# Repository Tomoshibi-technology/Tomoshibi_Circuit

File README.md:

# Tomoshibi_Circuit

ここは燈の基板フォルダです。

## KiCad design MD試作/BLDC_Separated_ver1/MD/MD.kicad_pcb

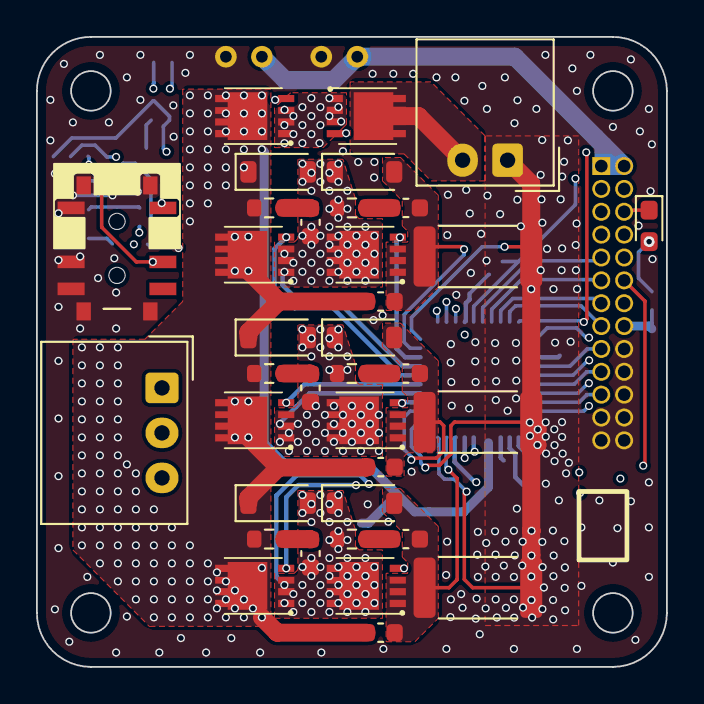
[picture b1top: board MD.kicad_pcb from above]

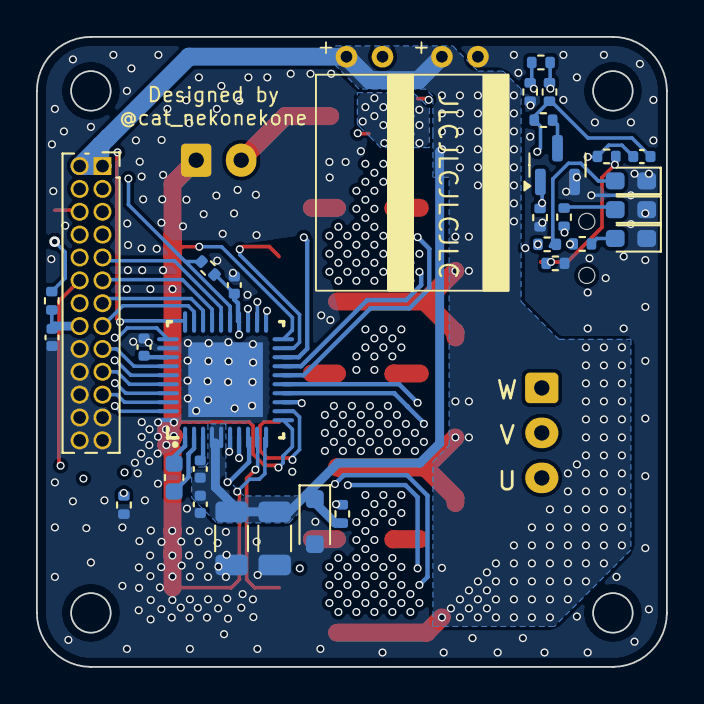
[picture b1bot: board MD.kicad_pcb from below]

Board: 4 copper layers, 35.0 x 35.0 mm, 68 parts (32 on the bottom side), 52 nets.

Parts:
C1, C25, C29: 0.1uF; C_0402_1005Metric
C2, C17: 100uF; Capacitor_Alum_Radial_5.0x11.0mm_Horizontal
C14, C26, C27: 1uF; C_0402_1005Metric
C23, C24: 10uF; C_1206_3216Metric
C28: 47nF; C_0603_1608Metric
C33, C34, C37, C38, C40, C41: CR_snub; C_0603_1608Metric
C35, C36, C39: C_snub; C_0603_1608Metric
D1, D20, D21, D22: Red; LED_0603_1608Metric_Pad1.05x0.95mm_HandSolder
D5: 1N5819WS; D_SOD-323_HandSoldering
D14, D15, D16, D17, D18, D19: SS2040FL; D_SOD-123
J4: Conn_02x13_Odd_Even; PinSocket_2x13_P1.27mm_Vertical
J5: Conn_01x02_Pin; Molex_SPOX_5268-02A_1x02_P2.50mm_Horizontal
J6: Conn_01x03_Pin; Molex_SPOX_5268-03A_1x03_P2.50mm_Horizontal
Q2, Q6: DI035P04PT; Package_TSON-Advance
Q5: BSS138; SOT-23
Q7, Q8, Q9, Q10, Q11, Q12: TPN19008QM; Package_TSON-Advance
R1: 1k; R_0402_1005Metric
R2, R3, R19, R24, R26, R28, R29: 10k; R_0402_1005Metric
R4: 100k; R_0402_1005Metric
R18: 47k; R_0402_1005Metric
R30, R69, R72, R75: 20k; R_0402_1005Metric
R56, R61, R66: 7m; R_2512_6332Metric
R67, R68, R70, R71, R73, R74: CR_snub; R_0603_1608Metric
SW4: SW_SPDT; SW_Slide_DPDT_SSSS820101
U6: Driver_FETGate_DRV8323S

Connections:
+3.3V: C1.1, C29.1, J4.16, R1.2, R2.2, R3.1, U6.24 (VREF)
/MotorDriver/BridgeA_S: C34.1, C35.1, D15.2 (A), Q7.1 (S), Q7.2 (S), Q7.3 (S), R56.2, U6.9 (SPA)
/MotorDriver/BridgeB_S: C36.1, C38.1, D17.2 (A), Q8.1 (S), Q8.2 (S), Q8.3 (S), R61.2, U6.12 (SPB)
/MotorDriver/BridgeC_S: C39.1, C41.1, D19.2 (A), Q12.1 (S), Q12.2 (S), Q12.3 (S), R66.2, U6.19 (SPC)
/MotorDriver/Phase_U: C33.1, D14.2 (A), D15.1 (K), J6.3, Q7.5 (D), Q10.1 (S), Q10.2 (S), Q10.3 (S), R68.2, R69.1, U6.7 (SHA)
/MotorDriver/Phase_V: C37.1, D16.2 (A), D17.1 (K), J6.2, Q8.5 (D), Q9.1 (S), Q9.2 (S), Q9.3 (S), R71.2, R72.1, U6.14 (SHB)
/MotorDriver/Phase_W: C40.1, D18.2 (A), D19.1 (K), J6.1, Q11.1 (S), Q11.2 (S), Q11.3 (S), Q12.5 (D), R74.2, R75.1, U6.17 (SHC)
/Power/24VBAT: J5.2, Q2.5 (D)
/Power/PowerSW: Q5.1 (G), R4.1, SW4.1 (A)
/Power/S-S: C14.1, Q2.1 (S), Q2.2 (S), Q2.3 (S), Q6.1 (S), Q6.2 (S), Q6.3 (S), R18.1, R26.1, R28.1
CAL: J4.14, U6.31 (CAL)
CS1_MD: J4.15, U6.29 (GAIN_SCS_N)
ENABLE: J4.4, U6.30 (ENABLE)
GND: C1.2, C2.2, C17.2, C23.2, C24.2, C25.2, C26.2, C29.2, D5.2 (A), D20.1 (K), D21.1 (K), D22.1 (K), J4.18, J4.20, J4.22, J4.23, J4.24, J4.25, J4.26, J5.1, Q5.2 (S), R3.2, R4.2, R19.2, R24.2, R30.2, R56.1, R61.1, R66.1, SW4.4 (shell), SW4.5 (shell), SW4.6 (shell), SW4.G1 (shell), SW4.G2 (shell), SW4.G3 (shell), SW4.G4 (shell), U6.10 (SNA), U6.11 (SNB), U6.20 (SNC), U6.32 (AGND), U6.40 (PGND), U6.41 (PAD)
INA_H: J4.17, U6.34 (INHA)
INA_L: J4.12, U6.35 (INLA)
INB_H: J4.19, U6.36 (INHB)
INB_L: J4.8, U6.37 (INLB)
INC_H: J4.21, U6.38 (INHC)
INC_L: J4.10, U6.39 (INLC)
MISO1: J4.9, U6.26 (MODE_SDO)
MOSI1: J4.11, U6.27 (IDRIVE_SDI)
unnamed: C33.2, R67.1
unnamed: C34.2, R68.1
unnamed: C37.2, R70.1
unnamed: C38.2, R71.1
unnamed: C40.2, R73.1
unnamed: C41.2, R74.1
unnamed: D1.2 (A), R1.1
unnamed: D20.2 (A), R69.2
unnamed: D21.2 (A), R72.2
unnamed: D22.2 (A), R75.2
unnamed: Q2.4 (G), R24.1, R26.2
unnamed: Q5.3 (D), R29.2
unnamed: C14.2, Q6.4 (G), R28.2, R29.1
unnamed: Q7.4 (G), U6.8 (GLA)
unnamed: Q8.4 (G), U6.13 (GLB)
unnamed: Q9.4 (G), U6.15 (GHB)
unnamed: Q10.4 (G), U6.6 (GHA)
unnamed: Q11.4 (G), U6.16 (GHC)
unnamed: Q12.4 (G), U6.18 (GLC)
unnamed: R18.2, R19.1, SW4.2 (B)
unnamed: C28.1, U6.2 (CPH)
unnamed: C28.2, U6.1 (CPL)
unnamed: C26.1, U6.33 (DVDD)
unnamed: C27.2, U6.3 (VCP)
SCLK1: J4.13, U6.28 (VDS_SCLK)
SOA: J4.7, U6.23 (SOA)
SOB: J4.5, U6.22 (SOB)
SOC: J4.3, U6.21 (SOC)
VDD: C2.1, C17.1, C23.1, C24.1, C25.1, C27.1, C35.2, C36.2, C39.2, D5.1 (K), D14.1 (K), D16.1 (K), D18.1 (K), J4.1, J4.2, Q6.5 (D), Q9.5 (D), Q10.5 (D), Q11.5 (D), R30.1, R67.2, R70.2, R73.2, U6.4 (VM), U6.5 (VDRAIN)
nFAULT: D1.1 (K), J4.6, R2.1, U6.25 (FAULT_N)

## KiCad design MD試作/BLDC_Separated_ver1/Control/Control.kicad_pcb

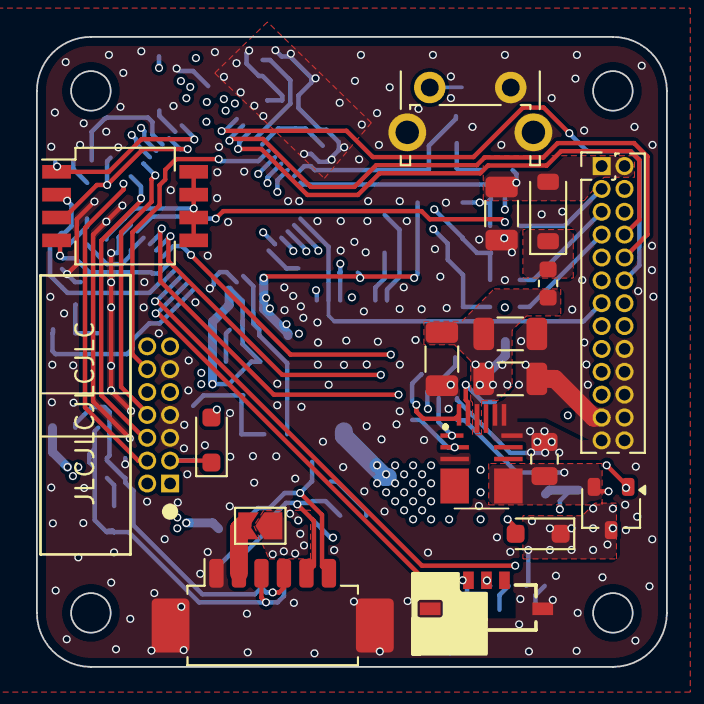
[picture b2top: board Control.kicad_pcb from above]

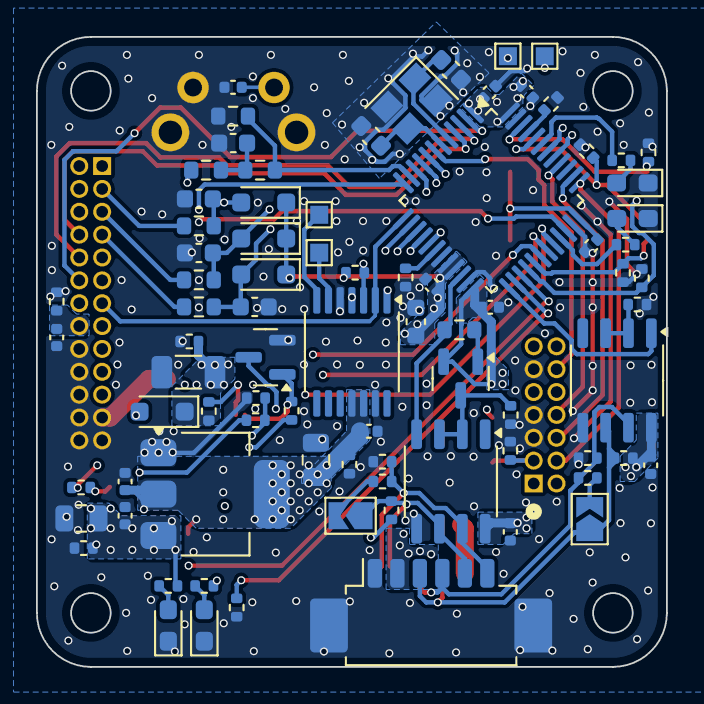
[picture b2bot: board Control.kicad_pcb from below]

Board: 4 copper layers, 35.0 x 35.0 mm, 100 parts (82 on the bottom side), 71 nets.

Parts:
C1, C2, C5, C6, C7, C8, C19, C20, C25: 0.1uF; C_0402_1005Metric
C3, C4: 22pF; C_0603_1608Metric
C9: 4.7uF; C_0603_1608Metric
C10, C14, C15, C26, C27: 10uF; C_1206_3216Metric
C11: 22uF; C_0805_2012Metric
C12, C13, C24: 1uF; C_0402_1005Metric
C16: 0.1uF; C_0603_1608Metric
C17, C18: 10uF; C_0805_2012Metric
C21, C22, C23: 330pF; C_0603_1608Metric
D1, D4, D6, D9, D10, D11: 1N5819WS; D_SOD-323_HandSoldering
D2, D3: Red; LED_0603_1608Metric_Pad1.05x0.95mm_HandSolder
D5: SS2040FL; D_SOD-123
D7, D8: Green; LED_0603_1608Metric_Pad1.05x0.95mm_HandSolder
IC1: DCDC_MPM3620A
J1: Conn_01x14_Pin; BoxHeader_2x07_P1.27mm_Horizontal
J2: Conn_02x13_Odd_Even; PinHeader_2x13_P1.27mm_Vertical
J3, J4: Conn_01x06_MountingPin; Molex_PicoBlade_53261-0671_1x06-1MP_P1.25mm_Horizontal
JP1, JP2: Jumper_2_Open; SolderJumper-2_P1.3mm_Open_TrianglePad1.0x1.5mm
JP3: SolderJumper_2_Open; SolderJumper-2_P1.3mm_Open_TrianglePad1.0x1.5mm
L1: 1uH; L_0603_1608Metric
Q1: BSS138; SOT-23
Q2: SSM3J332R; SOT-23W
Q3: S8550; SOT-23
R1, R3, R6, R7, R8, R13, R14, R16, R23, R31, R32, R33, R37: 10k; R_0402_1005Metric
R2: 1k; R_0402_1005Metric
R4, R5, R20, R21: 2k; R_0402_1005Metric
R9: 200k; R_0402_1005Metric
R10: 100k; R_0402_1005Metric
R11: 12k; R_0402_1005Metric
R12, R25, R26, R27, R28: 2.2k; R_0402_1005Metric
R15, R24: 20k; R_0402_1005Metric
R17: 1k; R_0603_1608Metric
R18: 75k; R_0603_1608Metric
R19: 10k; R_0603_1608Metric
R22: 7.5k; R_0603_1608Metric
R29, R30: 120; R_0402_1005Metric
R34, R35, R36: 100; R_0603_1608Metric
SW1: SW_SPST; SW_Tactile_SPST_Angled_PTS645Vx39-2LFS
SW3: SW_SPDT; SW_Slide_SPDT_SSAJ120100
SW4: SW_DIP_x04; SW_DIP_SPSTx04_Slide_Copal_CHS-04B_W7.62mm_P1.27mm
TP1, TP2, TP3, TP4: TestPoint; TestPoint_Pad_1.0x1.0mm
U1: STM32G473CET6; LQFP-48_7x7mm_P0.5mm
U2: AZ1117CH-3.3; SOT-223-3_TabPin2
U3, U4: MAX3485; SOP-8_3.9x4.9mm_P1.27mm
U5: Encoder_Magnetic_AS5047P; TSSOP-14_4.4x5mm_P0.65mm
Y1: 16MHz; Crystal_SMD_3225-4Pin_3.2x2.5mm

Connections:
+3.3V: C1.1, C2.1, C5.1, C6.1, C7.1, C9.2, C13.1, C18.1, C19.1, C20.1, C24.2, C25.1, D1.2 (A), D6.2 (A), D9.1 (K), D10.1 (K), D11.1 (K), J2.16, Q3.2 (E), R16.2, R21.2, R25.1, R27.1, R32.2, R37.1, SW3.2 (B), SW4.5, SW4.6, SW4.7, SW4.8, U1.1 (VBAT), U1.20 (VREF+), U1.21 (VDDA), U1.24 (VDD), U1.36 (VDD), U1.48 (VDD), U2.2 (VO), U3.8 (VCC), U4.8 (VCC), U5.11 (VDD5V), U5.12 (VDD3V)
+5V: C12.1, C17.1, D6.1 (K), Q2.3 (D), R14.2, R20.2, U2.3 (VI)
/Power/PG: IC1.18 (PG), Q1.1 (G), R10.1
/RS485/24V_IN: J3.2, JP3.1 (A)
/RS485/24V_OUT: J4.2, JP3.2 (B)
/RS485/RS485_A: J3.3, J4.3, JP1.1 (A), R25.2, U3.6 (A)
/RS485/RS485_B: J3.4, J4.4, R26.1, R29.2, U3.7 (B)
/RS485/RS485_X: J3.5, J4.5, JP2.1 (A), R27.2, U4.6 (A)
/RS485/RS485_Y: J3.6, J4.6, R28.1, R30.2, U4.7 (B)
BOOT0: R1.1, U1.45 (PB8-BOOT0)
CAL: J2.14, U1.27 (PB13)
CS1_Encoder: U1.16 (PB0), U5.1 (~CSn)
CS1_MD: J2.15, U1.17 (PB1)
Current_OUTA: C23.1, D9.2 (A), R34.2, U1.8 (PA0)
Current_OUTB: C22.1, D10.2 (A), R35.2, U1.9 (PA1)
Current_OUTC: C21.1, D11.2 (A), R36.2, U1.10 (PA2)
DIP_SW0: R6.2, SW4.1, U1.46 (PB9)
DIP_SW1: R7.2, SW4.2, U1.28 (PB14)
DIP_SW2: R31.2, SW4.3, U1.44 (PB7)
DIP_SW3: R33.2, SW4.4, U1.29 (PB15)
ENABLE: J2.4, U1.34 (PA12)
GND: C1.2, C2.2, C3.1, C4.1, C5.2, C6.2, C7.2, C8.2, C9.1, C10.2, C11.2, C12.2, C13.2, C14.2, C15.2, C16.2, C17.2, C18.2, C19.2, C20.2, C21.2, C22.2, C23.2, C24.1, C25.2, C26.2, C27.2, D2.1 (K), D3.1 (K), D7.1 (K), D8.1 (K), IC1.3 (AGND), IC1.12 (PGND), IC1.13 (PGND_2), IC1.14 (PGND_3), J1.5, J1.7, J1.11, J2.18, J2.20, J2.22, J2.23, J2.24, J2.25, J2.26, J3.1, J3.MP (MountPin), J4.1, J4.MP (MountPin), Q1.2 (S), R1.2, R2.2, R3.2, R6.1, R7.1, R8.2, R12.1, R14.1, R15.2, R16.1, R19.2, R23.2, R24.2, R26.2, R28.2, R31.1, R33.1, R37.2, SW1.2 (B), SW1.3 (shell), SW3.4 (shell), SW3.5 (shell), U1.19 (VSSA), U1.23 (VSS), U1.35 (VSS), U1.47 (VSS), U2.1 (GND), U3.5 (GND), U4.5 (GND), U5.5 (TEST), U5.13 (GND), Y1.2, Y1.4
HSE_IN: C3.2, U1.5 (PF0), Y1.1
HSE_OUT: C4.2, U1.6 (PF1), Y1.3
INA_H: J2.17, U1.30 (PA8)
INA_L: J2.12, U1.2 (PC13)
INB_H: J2.19, U1.31 (PA9)
INB_L: J2.8, U1.4 (PC15)
INC_H: J2.21, U1.32 (PA10)
INC_L: J2.10, U1.3 (PC14)
LED0: R4.2, U1.43 (PB6)
LED1: R5.2, U1.33 (PA11)
MISO1: J2.9, R32.1, U1.14 (PA6), U5.3 (MISO)
MOSI1: J2.11, U1.15 (PA7), U5.4 (MOSI)
MainRX3_RS485TX: U1.25 (PB11), U3.1 (RO)
MainTX3_RS485RX: R22.2, U1.22 (PB10), U4.4 (DI)
NRST: C8.1, J1.12, SW1.1 (A), U1.7 (NRST)
unnamed: C16.1, R17.2, R18.1
unnamed: D1.1 (K), J1.3, R2.1
unnamed: D2.2 (A), R4.1
unnamed: D3.2 (A), R5.1
unnamed: C11.1, D4.2 (A), IC1.9 (OUT), Q2.2 (S), R11.2, R13.1
unnamed: D5.1 (K), L1.1
unnamed: D7.2 (A), R20.1
unnamed: D8.2 (A), R21.1
unnamed: IC1.17 (EN), R9.1
unnamed: IC1.1 (FB), R11.1, R12.2
unnamed: IC1.2 (VCC), R10.2
unnamed: JP1.2 (B), R29.1
unnamed: JP2.2 (B), R30.1
unnamed: Q1.3 (D), Q2.1 (G), R13.2
unnamed: Q3.1 (B), R22.1
unnamed: Q3.3 (C), R24.1, U4.2 (~RE), U4.3 (DE)
unnamed: R3.1, U1.18 (PB2)
unnamed: R23.1, U3.2 (~RE), U3.3 (DE)
unnamed: TP3.1, U5.7 (A)
unnamed: TP2.1, U5.6 (B)
Phase_A: TP4.1, U1.41 (PB4)
Phase_B: TP1.1, U1.42 (PB5)
SCLK1: J2.13, U1.13 (PA5), U5.2 (CLK)
SOA: J2.7, R34.1
SOB: J2.5, R35.1
SOC: J2.3, R36.1
SWCLK: J1.6, U1.38 (PA14)
SWDIO: J1.4, U1.37 (PA13)
SWO: J1.8, U1.40 (PB3)
Slide_SW0: R8.1, SW3.1 (A), U1.26 (PB12)
VCC: C10.1, C15.1, C26.1, C27.1, D4.1 (K), IC1.16 (IN), L1.2, R9.2, R15.1
VDD: C14.1, D5.2 (A), J2.1, J2.2, R17.1
V_Meas.: R18.2, R19.1, U1.11 (PA3)
nFAULT: J2.6, U1.12 (PA4)

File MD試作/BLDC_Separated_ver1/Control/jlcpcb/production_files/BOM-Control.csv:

Comment,Designator,Footprint,LCSC,Quantity
1k,R2,R_0402_1005Metric,C11702,1
10uF,C15,C_1206_3216Metric,C13585,1
16MHz,Y1,Crystal_SMD_3225-4Pin_3.2x2.5mm,C13738,1
0.1uF,C16,C_0603_1608Metric,C14663,1
10uF,"C17,C18",C_0805_2012Metric,C15850,2
22pF,"C3,C4",C_0603_1608Metric,C1653,2
330pF,"C21,C22,C23",C_0603_1608Metric,C1664,3
1N5819WS,"D10,D11,D4,D9",D_SOD-323_HandSoldering,C191023,4
4.7uF,C9,C_0603_1608Metric,C19666,1
1k,R17,R_0603_1608Metric,C21190,1
100,"R34,R35,R36",R_0603_1608Metric,C22775,3
7.5k,R22,R_0603_1608Metric,C23234,1
75k,R18,R_0603_1608Metric,C23242,1
120,"R29,R30",R_0402_1005Metric,C25079,2
100k,R10,R_0402_1005Metric,C25741,1
10k,"R1,R13,R14,R16,R23,R3,R31,R32,R33,R37,R6,R7,R8",R_0402_1005Metric,C25744,13
12k,R11,R_0402_1005Metric,C25752,1
200k,R9,R_0402_1005Metric,C25764,1
20k,"R15,R24",R_0402_1005Metric,C25765,2
10k,R19,R_0603_1608Metric,C25804,1
2.2k,"R12,R25,R26,R27,R28",R_0402_1005Metric,C25879,5
0.1uF,"C1,C19,C2,C20,C25,C5,C6,C7,C8",C_0402_1005Metric,C307331,9
2k,"R20,R21,R4,R5",R_0402_1005Metric,C4109,4
BSS138,Q1,SOT-23,C5224274,1
1uF,"C12,C13,C24",C_0402_1005Metric,C52923,3
MAX3485,"U3,U4",SOP-8_3.9x4.9mm_P1.27mm,C558792,2
S8550,Q3,SOT-23,C8542,1

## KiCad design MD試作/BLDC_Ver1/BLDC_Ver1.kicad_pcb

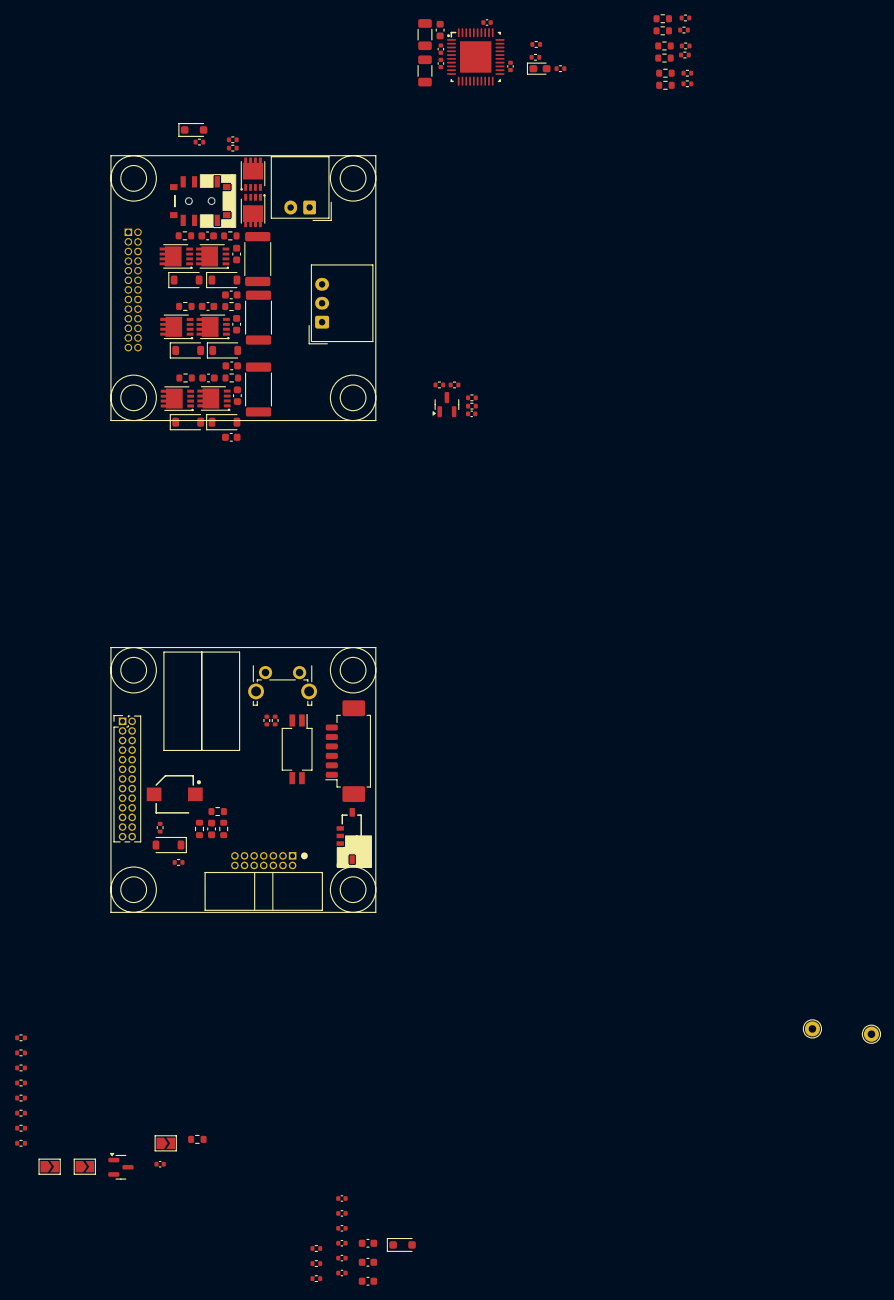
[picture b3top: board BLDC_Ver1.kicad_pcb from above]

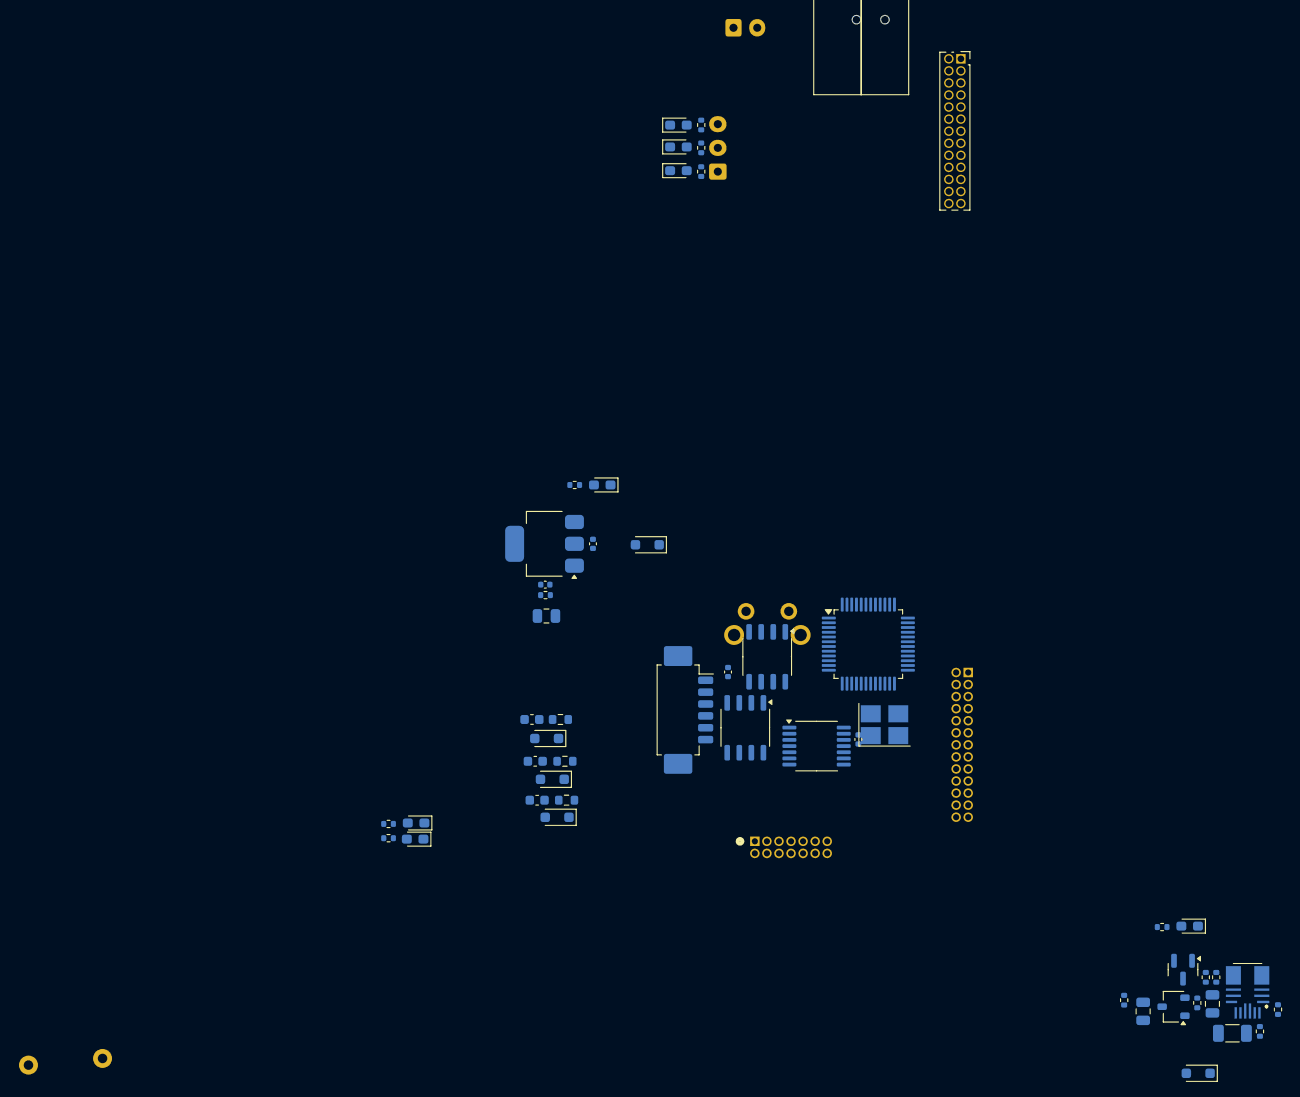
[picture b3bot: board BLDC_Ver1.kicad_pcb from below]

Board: 2 copper layers, 165 parts (51 on the bottom side), 94 nets, no tracks yet.

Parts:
C1, C2, C5, C6, C7, C8, C10, C11, C25, C29: 0.1uF; C_0402_1005Metric
C3, C4: 22pF; C_0603_1608Metric
C9: 4.7uF; C_0603_1608Metric
C12, C23, C24: 10uF; C_1206_3216Metric
C13: 22uF; C_0805_2012Metric
C14, C15, C16, C22, C26, C27: 1uF; C_0402_1005Metric
C19: 0.1uF; C_0603_1608Metric
C20, C21: 10uF; C_0805_2012Metric
C28: 47nF; C_0603_1608Metric
C30, C31, C32: 330pF; C_0603_1608Metric
C33, C34, C37, C38, C40, C41: CR_snub; C_0603_1608Metric
C35, C36, C39: C_snub; C_0603_1608Metric
D1, D4, D5, D7, D10, D11, D12: 1N5819WS; D_SOD-323_HandSoldering
D2, D3, D13, D20, D21, D22: Red; LED_0603_1608Metric_Pad1.05x0.95mm_HandSolder
D6, D14, D15, D16, D17, D18, D19: SS2040FL; D_SOD-123
D8, D9: Green; LED_0603_1608Metric_Pad1.05x0.95mm_HandSolder
IC1: DCDC_MPM3620A
J1: Conn_01x14_Pin; BoxHeader_2x07_P1.27mm_Horizontal
J2, J3: Conn_01x06_MountingPin; Molex_PicoBlade_53261-0671_1x06-1MP_P1.25mm_Horizontal
J4: Conn_01x26_Socket; PinSocket_2x13_P1.27mm_Vertical
J5: Conn_01x02_Pin; Molex_SPOX_5268-02A_1x02_P2.50mm_Horizontal
J6: Conn_01x03_Pin; Molex_SPOX_5268-03A_1x03_P2.50mm_Horizontal
J7: Conn_01x26_Pin; PinHeader_2x13_P1.27mm_Vertical
JP1, JP2: Jumper_2_Open; SolderJumper-2_P1.3mm_Open_TrianglePad1.0x1.5mm
JP3: SolderJumper_2_Open; SolderJumper-2_P1.3mm_Open_TrianglePad1.0x1.5mm
L1: 22uH; Inductor_CDPH4D19F
Q1: S8550; SOT-23
Q2, Q6: DI035P04PT; Package_TSON-Advance
Q3, Q5: BSS138; SOT-23
Q4: SSM3J332R; SOT-23W
Q7, Q8, Q9, Q10, Q11, Q12: TPN19008QM; Package_TSON-Advance
R1, R3, R6, R7, R8, R10, R18, R19, R24, R25, R26, R27, R28, R29, R30, R31, R32, R47, R48, R54, R55, R59, R60, R64, R65: 10k; R_0402_1005Metric
R2, R38: 1k; R_0402_1005Metric
R4, R5, R36, R37: 2k; R_0402_1005Metric
R9: 7.5k; R_0603_1608Metric
R11, R69, R72, R75: 20k; R_0402_1005Metric
R12, R13, R14, R15, R23: 2.2k; R_0402_1005Metric
R16, R17: 120; R_0402_1005Metric
R20: 200k; R_0402_1005Metric
R21: 100k; R_0402_1005Metric
R22: 12k; R_0402_1005Metric
R33: 1k; R_0603_1608Metric
R34: 75k; R_0603_1608Metric
R35: 10k; R_0603_1608Metric
R49, R50, R51: 100; R_0603_1608Metric
R52, R53, R57, R58, R62, R63: 0; R_0603_1608Metric
R56, R61, R66: 7m; R_2512_6332Metric
R67, R68, R70, R71, R73, R74: CR_snub; R_0603_1608Metric
SW1: SW_SPST; SW_Tactile_SPST_Angled_PTS645Vx39-2LFS
SW2: SW_DIP_x02; SW_DIP_SPSTx02_Slide_Copal_CHS-02B_W7.62mm_P1.27mm
SW3: SW_SPDT; SW_Slide_DPDT_SSAJ120100
SW4: SW_SPDT; SW_Slide_SPDT_SSSS820101
TP1, TP2: TestPoint; TestPoint_THTPad_D2.0mm_Drill1.0mm
U1: STM32G473CET6; LQFP-48_7x7mm_P0.5mm
U2, U3: MAX3485; SOP-8_3.9x4.9mm_P1.27mm
U4: AZ1117CH-3.3; SOT-223-3_TabPin2
U5: Encoder_Magnetic_AS5047P; TSSOP-14_4.4x5mm_P0.65mm
U6: Driver_FETGate_DRV8323S
Y1: 16MHz; Crystal_SMD_3225-4Pin_3.2x2.5mm_HandSoldering

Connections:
+3.3V: C1.1, C2.1, C5.1, C6.1, C7.1, C9.2, C10.1, C11.1, C16.1, C20.1, C22.2, C29.1, D1.2 (A), D7.2 (A), D10.1 (K), D11.1 (K), D12.1 (K), Q1.2 (E), R12.1, R14.1, R32.2, R37.2, R38.2, R47.2, R48.2, SW2.3, SW2.4, SW3.2 (B), TP1.1, U1.1 (VBAT), U1.20 (VREF+), U1.21 (VDDA), U1.24 (VDD), U1.36 (VDD), U1.48 (VDD), U2.8 (VCC), U3.8 (VCC), U4.2 (VO), U5.11 (VDD5V), U5.12 (VDD3V), U6.24 (VREF)
+5V: C15.1, C21.1, D7.1 (K), Q4.3 (D), R27.2, R36.2, U4.3 (VI)
/MotorDriver/BridgeA_S: C34.1, C35.1, D15.2 (A), Q7.1 (S), Q7.2 (S), Q7.3 (S), R55.2, R56.2, U6.9 (SPA)
/MotorDriver/BridgeB_S: C36.1, C38.1, D17.2 (A), Q8.1 (S), Q8.2 (S), Q8.3 (S), R60.1, R61.2, U6.12 (SPB)
/MotorDriver/BridgeC_S: C39.1, C41.1, D19.2 (A), Q12.1 (S), Q12.2 (S), Q12.3 (S), R65.1, R66.2, U6.19 (SPC)
/MotorDriver/Phase_U: C33.1, D14.2 (A), D15.1 (K), J6.1, Q7.5 (D), Q10.1 (S), Q10.2 (S), Q10.3 (S), R54.2, R68.2, R69.1, U6.7 (SHA)
/MotorDriver/Phase_V: C37.1, D16.2 (A), D17.1 (K), J6.2, Q8.5 (D), Q9.1 (S), Q9.2 (S), Q9.3 (S), R59.1, R71.2, R72.1, U6.14 (SHB)
/MotorDriver/Phase_W: C40.1, D18.2 (A), D19.1 (K), J6.3, Q11.1 (S), Q11.2 (S), Q11.3 (S), Q12.5 (D), R64.1, R74.2, R75.1, U6.17 (SHC)
/MotorDriver/SOA: R49.1, U6.23 (SOA)
/MotorDriver/SOB: R50.1, U6.22 (SOB)
/MotorDriver/SOC: R51.1, U6.21 (SOC)
/Power/24VBAT: J5.2, Q2.5 (D)
/Power/PG: IC1.18 (PG), Q3.1 (G), R21.1
/Power/PowerSW: Q5.1 (G), R18.2, R19.1
/Power/S-S: C14.1, Q2.1 (S), Q2.2 (S), Q2.3 (S), Q6.1 (S), Q6.2 (S), Q6.3 (S), R26.1, R28.1, SW4.2 (B)
/RS485/24V_IN: J2.2, JP3.1 (A)
/RS485/24V_OUT: J3.2, JP3.2 (B)
/RS485/RS485_A: J2.3, J3.3, JP1.1 (A), R12.2, U2.6 (A)
/RS485/RS485_B: J2.4, J3.4, R13.1, R16.2, U2.7 (B)
/RS485/RS485_X: J2.5, J3.5, JP2.1 (A), R14.2, U3.6 (A)
/RS485/RS485_Y: J2.6, J3.6, R15.1, R17.2, U3.7 (B)
BOOT0: R1.1, U1.45 (PB8-BOOT0)
Current_OUTA: C32.1, D10.2 (A), R49.2, U1.8 (PA0)
Current_OUTB: C31.1, D11.2 (A), R50.2, U1.9 (PA1)
Current_OUTC: C30.1, D12.2 (A), R51.2, U1.10 (PA2)
DIP_SW0: R6.2, R7.2, SW2.1, SW2.2
GND: C1.2, C2.2, C3.1, C4.1, C5.2, C6.2, C7.2, C8.2, C9.1, C10.2, C11.2, C12.2, C13.2, C15.2, C16.2, C19.2, C20.2, C21.2, C22.1, C23.2, C24.2, C25.2, C26.2, C29.2, C30.2, C31.2, C32.2, D2.1 (K), D3.1 (K), D5.2 (A), D8.1 (K), D9.1 (K), D20.1 (K), D21.1 (K), D22.1 (K), IC1.3 (AGND), IC1.12 (PGND), IC1.13 (PGND_2), IC1.14 (PGND_3), J1.5, J1.7, J1.11, J2.1, J2.MP (MountPin), J3.1, J3.MP (MountPin), J5.1, Q3.2 (S), Q5.2 (S), R1.2, R2.2, R3.2, R6.1, R7.1, R8.2, R10.2, R11.2, R13.2, R15.2, R19.2, R23.1, R24.2, R27.1, R30.2, R31.2, R32.1, R35.2, R56.1, R61.1, R66.1, SW1.2 (B), TP2.1, U1.19 (VSSA), U1.23 (VSS), U1.35 (VSS), U1.47 (VSS), U2.5 (GND), U3.5 (GND), U4.1 (GND), U5.5 (TEST), U5.13 (GND), U6.10 (SNA), U6.11 (SNB), U6.20 (SNC), U6.32 (AGND), U6.40 (PGND), U6.41 (PAD), Y1.2, Y1.4
HSE_IN: C3.2, U1.5 (PF0), Y1.1
HSE_OUT: C4.2, U1.6 (PF1), Y1.3
INA_H: U1.30 (PA8), U6.34 (INHA)
INB_H: U1.31 (PA9), U6.36 (INHB)
INC_H: U1.32 (PA10), U6.38 (INHC)
MISO1: R47.1, U1.14 (PA6), U5.3 (MISO), U6.26 (MODE_SDO)
MOSI1: U1.15 (PA7), U5.4 (MOSI), U6.27 (IDRIVE_SDI)
MainRX3_RS485TX: U1.25 (PB11), U2.1 (RO)
MainTX3_RS485RX: R9.2, U1.22 (PB10), U3.4 (DI)
NRST: C8.1, J1.12, SW1.1 (A), U1.7 (NRST)
unnamed: C19.1, R33.2, R34.1
unnamed: C33.2, R67.1
unnamed: C34.2, R68.1
unnamed: C37.2, R70.1
unnamed: C38.2, R71.1
unnamed: C40.2, R73.1
unnamed: C41.2, R74.1
unnamed: D1.1 (K), J1.3, R2.1
unnamed: D2.2 (A), R4.1
unnamed: D3.2 (A), R5.1
unnamed: C13.1, D4.2 (A), IC1.9 (OUT), Q4.2 (S), R22.2, R25.1
unnamed: D6.1 (K), L1.1
unnamed: D8.2 (A), R36.1
unnamed: D9.2 (A), R37.1
unnamed: D13.2 (A), R38.1
unnamed: D20.2 (A), R69.2
unnamed: D21.2 (A), R72.2
unnamed: D22.2 (A), R75.2
unnamed: IC1.17 (EN), R20.1
unnamed: IC1.1 (FB), R22.1, R23.2
unnamed: IC1.2 (VCC), R21.2
unnamed: JP1.2 (B), R16.1
unnamed: JP2.2 (B), R17.1
unnamed: Q1.1 (B), R9.1
unnamed: Q1.3 (C), R11.1, U3.2 (~RE), U3.3 (DE)
unnamed: Q2.4 (G), R24.1, R26.2
unnamed: Q3.3 (D), Q4.1 (G), R25.2
unnamed: Q5.3 (D), R29.2
unnamed: C14.2, Q6.4 (G), R28.2, R29.1
unnamed: Q7.4 (G), R53.2, R55.1
unnamed: Q8.4 (G), R58.2, R60.2
unnamed: Q9.4 (G), R57.2, R59.2
unnamed: Q10.4 (G), R52.2, R54.1
unnamed: Q11.4 (G), R62.2, R64.2
unnamed: Q12.4 (G), R63.2, R65.2
unnamed: R18.1, SW4.1 (A)
unnamed: R3.1, U1.18 (PB2)
unnamed: R10.1, U2.2 (~RE), U2.3 (DE)
unnamed: C28.1, U6.2 (CPH)
unnamed: C28.2, U6.1 (CPL)
unnamed: C26.1, U6.33 (DVDD)
unnamed: R52.1, U6.6 (GHA)
unnamed: R57.1, U6.15 (GHB)
unnamed: R62.1, U6.16 (GHC)
unnamed: R53.1, U6.8 (GLA)
unnamed: R58.1, U6.13 (GLB)
unnamed: R63.1, U6.18 (GLC)
unnamed: C27.2, U6.3 (VCP)
SCLK1: U1.13 (PA5), U5.2 (CLK), U6.28 (VDS_SCLK)
SWCLK: J1.6, U1.38 (PA14)
SWDIO: J1.4, U1.37 (PA13)
SWO: J1.8, U1.40 (PB3)
Slide_SW0: R8.1, SW3.1 (A)
VCC: C12.1, D4.1 (K), IC1.16 (IN), L1.2, R20.2, R31.1
VDD: C23.1, C24.1, C25.1, C27.1, C35.2, C36.2, C39.2, D5.1 (K), D6.2 (A), D14.1 (K), D16.1 (K), D18.1 (K), Q6.5 (D), Q9.5 (D), Q10.5 (D), Q11.5 (D), R30.1, R33.1, R67.2, R70.2, R73.2, U6.4 (VM), U6.5 (VDRAIN)
V_Meas.: R34.2, R35.1, U1.11 (PA3)
nFAULT: D13.1 (K), R48.1, U6.25 (FAULT_N)

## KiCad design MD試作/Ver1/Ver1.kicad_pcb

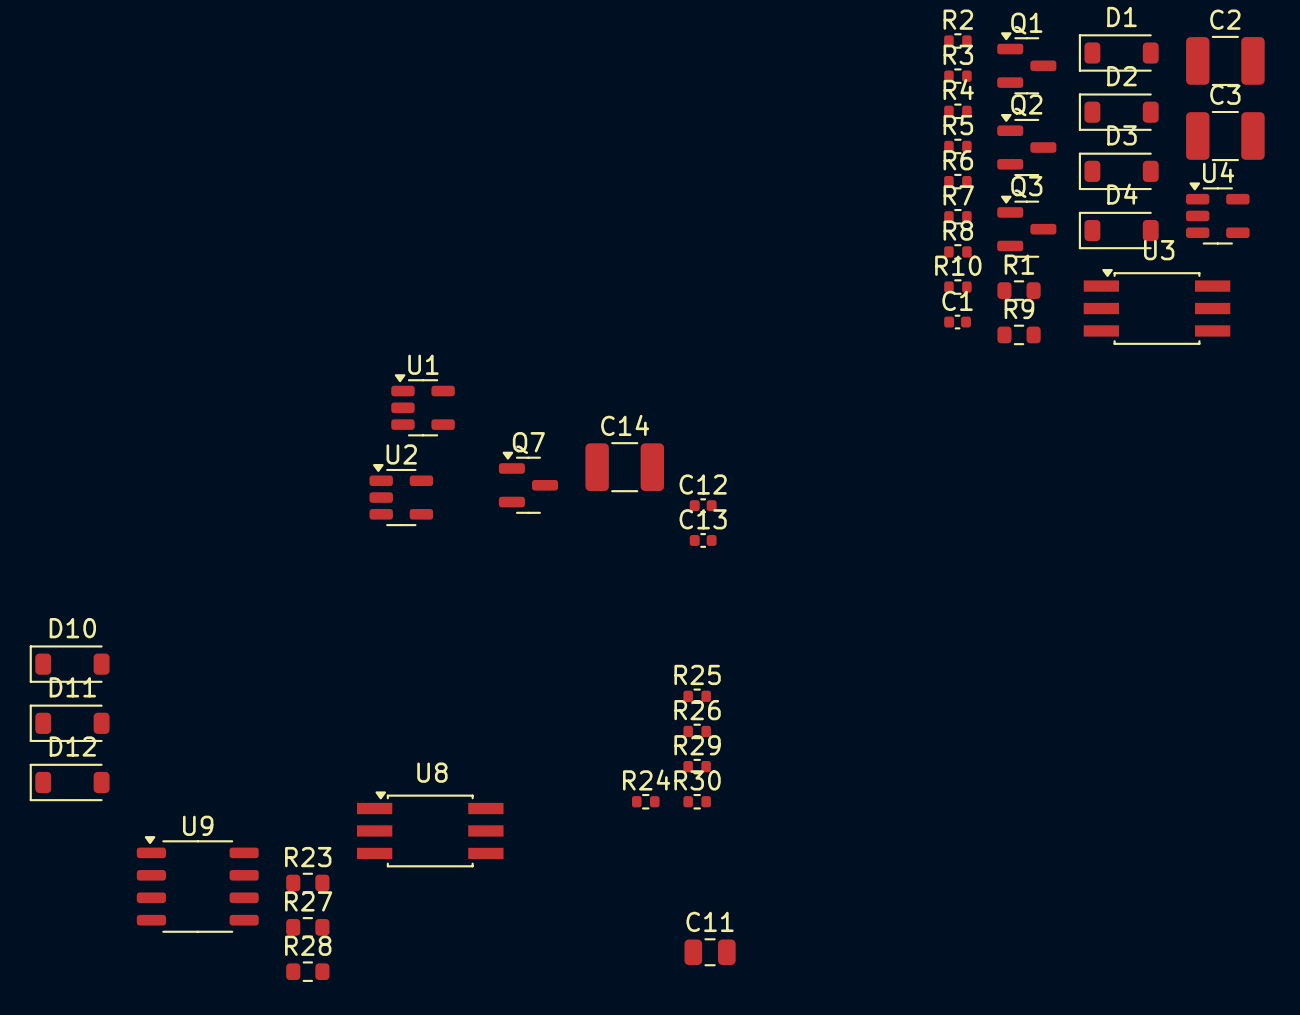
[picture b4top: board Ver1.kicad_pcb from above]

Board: 2 copper layers, 42 parts (0 on the bottom side), 28 nets, no tracks yet.

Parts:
C1, C12, C13: 0.1uF; C_0402_1005Metric
C2, C3, C14: C; C_1210_3225Metric_Pad1.33x2.70mm_HandSolder
C11: 10uF; C_0805_2012Metric
D1, D2, D3, D4, D10, D11, D12: SS2040FL; D_SOD-123
Q1, Q2, Q3, Q7: BSS138; SOT-23
R1, R23: 47; R_0603_1608Metric
R2, R4, R10, R24, R26, R29, R30: 10k; R_0402_1005Metric
R3, R25: 470; R_0402_1005Metric
R5, R6, R7, R8: 1k; R_0402_1005Metric
R9, R27, R28: 10; R_0603_1608Metric
U1, U2, U4: MCP1402; SOT-23-5
U3, U8: TLP2361; SO-6_4.4x3.6mm_P1.27mm
U9: IR2302; SOP-8_3.9x4.9mm_P1.27mm

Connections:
+3.3V: R3.1, R25.1
+5V: C1.1, C12.1, U3.6 (VDD), U8.6 (VDD)
GND: C1.2, C11.2, C12.2, C13.2, D12.2 (A), Q1.2 (S), Q2.2 (S), Q3.2 (S), Q7.2 (S), R2.1, R4.1, R24.1, R26.1, R30.1, U2.1 (GND), U2.4 (GND), U3.3 (K), U3.4 (GND), U8.3 (K), U8.4 (GND), U9.4 (COM)
unnamed: C2.1, D1.1 (K), R5.2, U1.2 (Vdd)
unnamed: D2.1 (K), R6.1, U1.3 (IN)
unnamed: C3.2, D3.2 (A), R10.1, U4.1 (GND), U4.4 (GND)
unnamed: D3.1 (K), R8.1
unnamed: C3.1, D4.1 (K), R7.2, U4.2 (Vdd)
unnamed: C14.1, D10.1 (K), U9.8 (VB)
unnamed: C2.2, D2.2 (A), D11.2 (A), D12.1 (K), R29.1, U1.1 (GND), U1.4 (GND)
unnamed: Q1.3 (D), R3.2, U3.1 (A)
unnamed: Q1.1 (G), R1.2, R2.2
unnamed: Q2.3 (D), R5.1, R6.2
unnamed: Q3.3 (D), R7.1, R8.2
unnamed: Q7.3 (D), R25.2, U8.1 (A)
unnamed: Q7.1 (G), R23.2, R24.2
unnamed: R27.2, R29.2
unnamed: R28.2, R30.2
unnamed: R9.2, R10.2
unnamed: R27.1, U1.5 (OUT)
unnamed: R28.1, U2.5 (OUT)
unnamed: R4.2, U3.5 (VO)
unnamed: R9.1, U4.5 (OUT)
unnamed: R26.2, U8.5 (VO), U9.2 (IN)
unnamed: C14.2, U9.6 (VS)
PWM_A: R1.1, R23.1
VCC: C13.1, D10.2 (A), U9.1 (VCC)
Vdrive: C11.1, D1.2 (A), D4.2 (A), D11.1 (K)
